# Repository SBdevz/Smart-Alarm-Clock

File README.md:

# ESP32 Smart Alarm Clock

This is a smart alarm clock that uses an ESP32 to control the system.

It includes an OLED display that shows weather conditions and temperature, a buzzer that sounds an alarm, and a button for settings.

Right now, there is a basic schematic of the PCB and a small program in this repository. The project is a work in progress, so I will make final changes when the PCB arrives!

### Features
* Uses the ESP32 Chip to read online data
* Displays weather conditions and temperature using online data
* Includes a button for easy navigation
* Pocket-sized and easy to carry
* Works as a normal alarm clock as well

### Upcoming
* The board needs to be ordered
* Parts will be soldered
* Program needs to be completed
* There will be a CAD-designed shell to hold all components together

### Licence
* **MIT Licence**

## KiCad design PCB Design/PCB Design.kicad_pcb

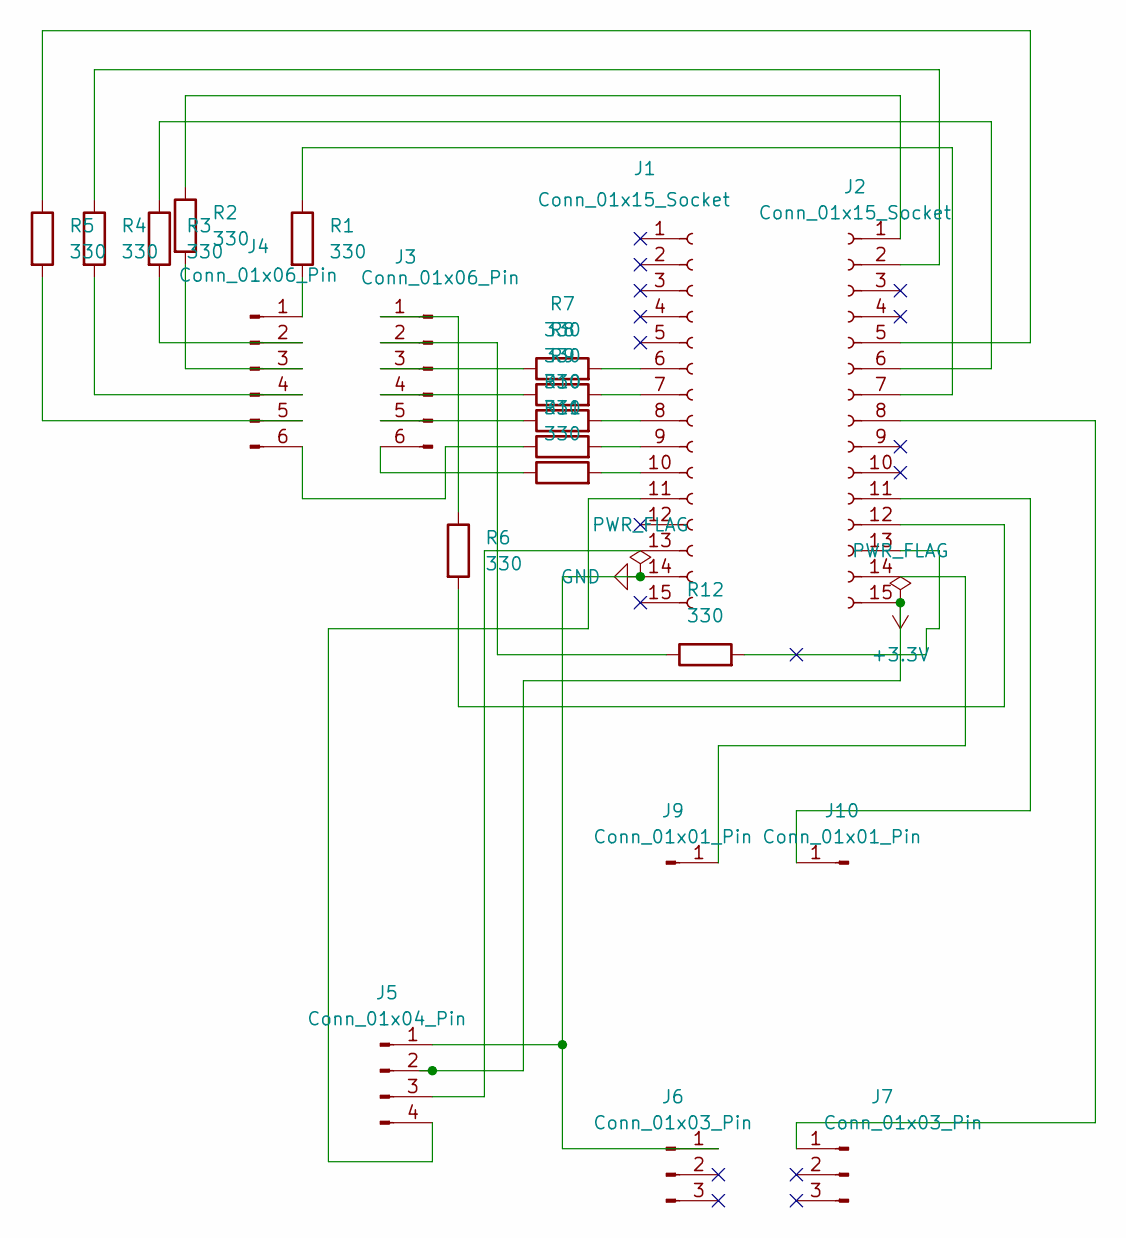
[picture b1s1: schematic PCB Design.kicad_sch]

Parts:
J1, J2: Conn_01x15_Socket; PinSocket_1x15_P2.54mm_Vertical
J3, J4: Conn_01x06_Pin; Altech_AK100_1x06_P5.00mm
J5: Conn_01x04_Pin; Altech_AK100_1x04_P5.00mm
J6, J7: Conn_01x03_Pin; Altech_AK100_1x03_P5.00mm
J9, J10: Conn_01x01_Pin; Pin_D1.1mm_L10.2mm_W3.5mm_Flat
R1, R2, R3, R4, R5, R6, R7, R8, R9, R10, R11, R12: 330; R_Axial_DIN0207_L6.3mm_D2.5mm_P7.62mm_Horizontal

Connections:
+3.3V: J2.15, J5.2
GND: J1.14, J5.1, J6.1 (Pin_1_1)
unnamed: J1.6, R7.2
unnamed: J1.7, R8.2
unnamed: J1.8, R9.2
unnamed: J1.9, R10.2
unnamed: J1.10, R11.2
unnamed: J1.11, J5.4
unnamed: J1.13, J5.3
unnamed: J2.1, R2.1
unnamed: J2.2, R4.1
unnamed: J2.5, R5.1
unnamed: J2.6, R3.1
unnamed: J2.7, R1.1
unnamed: J2.8, J7.1 (Pin_1_1)
unnamed: J2.12, R6.2
unnamed: J2.13, R12.2
unnamed: J2.14, J9.1 (Pin_1_1)
unnamed: J3.1, R6.1
unnamed: J3.2, R12.1
unnamed: J3.3, R7.1
unnamed: J3.4, R8.1
unnamed: J3.5, R9.1
unnamed: J3.6, R11.1
unnamed: J4.1, R1.2
unnamed: J4.2, R3.2
unnamed: J4.3, R2.2
unnamed: J4.4, R4.2
unnamed: J4.5, R5.2
unnamed: J4.6, R10.1
unnamed: J2.11, J10.1 (Pin_1_1)

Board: 2 copper layers, 21 parts (0 on the bottom side), 31 nets, no tracks yet.
